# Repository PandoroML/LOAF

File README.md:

# LOAF (Local Observations and Atmospheric Forecasting)

Open source hyperlocal weather forecasting combining machine learning forecast models with local station observations.

- Do you want to improve the weather forecasts at a specific place? 
- Do you have access to local sensors or are intersted in building them? 
- Are you interested in understanding the full process and not relying on big tech companies hiding proprietary algorithms to do so? 

If you answered yes to all of the above, then LOAF is for you.

Part of [Pandoro](https://pandoro.today) — Bread Board Foundry's open science ML tools for climate and environmental research.

This is definitely a work in progress, so stay tuned!

## Planned Architecture

```
┌─────────────────┐      ┌─────────────────────────────────────┐      ┌─────────────────┐
│  DIY Sensors    │ ──── │          Raspberry Pi               │ ──── │ Home Assistant  │
│  (Anemometer,   │      │  • Data storage                     │      │                 │
│   Temperature,  │      │  • ML forecast processing           │      │  Weather entity │
│   etc.)         │      │  • Local prediction generation      │      │  integrations   │
└─────────────────┘      └─────────────────────────────────────┘      └─────────────────┘
```

**Data Flow:**
1. **Sensors → Raspberry Pi**: Local sensors connect to the Pi via a common sensors library, logging observations to local storage
2. **Forecast Processing**: The Pi runs the trained ML model, combining local sensor data with regional forecasts (HRRR/GFS) to generate hyperlocal predictions
3. **Home Assistant Integration**: Predictions are exposed as Home Assistant entities, allowing integration with automations, dashboards, and alerts

## Latest Cool Picture

The first of the ultrasonic transducers have arrived!

## Current priorities:

- Set up HRRR/MADIS data pipeline
- Train regional model and validate against local observations
- Deploy the model to local hardware (raspberry pi)
- Create Home Assistant widget for local wind predictions

---

## Why LOAF?

Standard weather forecasts operate on 3km grids. That resolution can't capture the wind patterns at your specific site—whether it's a backyard wind turbine, a fire-prone hillside, or a remote research station.

Recent ML research shows that fusing gridded forecasts with local sensor data via transformers can reduce prediction error by up to 80%. Commercial services like Tomorrow.io offer this, but they're proprietary and subscription-based. The academic code exists, but there's no easy way to go from "I have a Raspberry Pi" to "I have an improved local forecast."

LOAF bridges that gap: open source hardware, open source models, no vendor lock-in. Build a sensor, train a model for your region, run inference locally.

## About

LOAF generates hyperlocal weather forecasts for locations without nearby weather stations by combining:

- Regional forecast models (NOAA GFS, HRRR, ERA5)
- Sparse local weather station observations
- Multi-modal transformer architecture for spatial-temporal fusion

**Built on research from MIT Earth Intelligence Lab:**
- GitHub: [Earth-Intelligence-Lab/LocalizedWeather](https://github.com/Earth-Intelligence-Lab/LocalizedWeather)
- Paper: Yang, Q., et al. (2024). *Local Off-Grid Weather Forecasting with Multi-Modal Earth Observation Data.* [arXiv:2410.12938](https://arxiv.org/abs/2410.12938)

## Hardware

LOAF uses open source hardware with no vendor lock-in:

- **Sensor**: DIY ultrasonic anemometer
- **Logger**: Raspberry Pi with RS-485/SDI-12 interface and 3D printed enclosure for predictions
- **Power**: Solar panel + battery for remote deployment

## Use Cases

- Off-grid environmental monitoring sites
- Research locations without dedicated weather infrastructure
- Applications requiring forecast transparency and hardware specifications for reproducibility

## Features

- Corrects systematic biases in large-scale forecast models for local conditions
- Hardware-transparent infrastructure for reproducible research
- Clear documentation for researchers without ML engineering backgrounds
- Combines numerical weather predictions with station measurements

## Related Projects

- [offgrid-weather-station](https://github.com/vinthewrench/offgrid-weather-station) - Off-grid weather station project
- [QingStation](https://github.com/majianjia/QingStation) - Open source ultrasonic anemometer
- [DL1GLH Ultrasonic Anemometer](https://www.dl1glh.de/ultrasonic-anemometer.html) - DIY ultrasonic wind sensor design

## Documentation

See the full documentation here: https://pandoroml.github.io/LOAF/

### Development Plans

- [ML Pipeline Development Plan](plan/dev-plan-ml-pipeline.md) - Detailed plan for reproducing LocalizedWeather for Seattle/PNW

### How to Run

The pipeline is: **download data → train a model → serve forecasts over REST**. Commands
below assume you're in the repo root and have installed the package (`pip install -e ".[dev]"`).
They use `config/arlington.yaml` (DCA, IAD, BWI, HEF, MRB stations); swap in
`config/seattle.yaml` for the PNW region instead.

#### Quickest path: one command

`loaf-pipeline` chains download → train → serve for you:

```bash
loaf-pipeline --config software/config/arlington.yaml \
    --start-date 2024-10-01 --end-date 2024-12-31 --year 2024 --port 5000
```

It blocks on the running server at the end, so leave it running and query it from another
terminal (see step 4 below). Useful flags for resuming a partial run:

- `--skip-download` — reuse whatever's already in `data/`
- `--skip-train --checkpoint <path>` — skip straight to serving an existing checkpoint
- `--no-serve` — stop after training, print the checkpoint path, and exit
- `--use-hrrr` / `--use-era5` — also download and fuse gridded forecasts (see step 1)

Run `loaf-pipeline --help` for the full flag list (it's the union of the three commands below).

Run loaf-report-summary --runs-dir runs after any batch of training runs to summarize results all modeling attempts in /runs.

#### Or, step by step

Useful if you want to inspect data between steps, retrain from already-downloaded data, or
swap in a different checkpoint without retraining.

**1. Download station observations** (IEM/ASOS — no registration required):

```bash
loaf-download-iem --config software/config/arlington.yaml \
    --start-date 2024-10-01 --end-date 2024-12-31
```

This is the minimum needed to train. Optionally fuse gridded forecasts too — HRRR needs no
auth (AWS S3), ERA5 needs a free [CDS API key](https://cds.climate.copernicus.eu/) in
`~/.cdsapirc`:

```bash
loaf-download-hrrr --config software/config/arlington.yaml \
    --start-date 2024-10-01 --end-date 2024-12-31
loaf-download-era5 --config software/config/arlington.yaml \
    --start-year 2024 --end-year 2024
```

All three write into `data/` in the current directory by default.

**2. Train a model** (MPNN or ViT backbone):

```bash
loaf-train --config software/config/arlington.yaml --year 2024
# add --model-type vit, --epochs N, --use-hrrr, or --use-era5 as needed
```

Writes `best.pt` / `last.pt` checkpoints and a `train_log.csv` to `runs/arlington_<timestamp>/`.

**3. Serve forecasts over REST:**

```bash
loaf-serve --checkpoint runs/arlington_<timestamp>/best.pt --port 5000
```

**4. Query it** (e.g. Reagan National Airport, Arlington VA):

```bash
curl "http://localhost:5000/api/forecast?lat=38.8512&lon=-77.0402"
curl http://localhost:5000/api/forecast/all   # every station in the graph
curl http://localhost:5000/health
```

Each response includes multi-horizon `u`/`v` wind predictions plus derived `wind_speed` and
`wind_direction`, ready to wire into a Home Assistant REST sensor.

## License

MIT

## Citation

If you find this project useful for your research or applications, please kindly cite using this BibTeX::
```bibtex
@software{Johnson_LOAF_Local_Observations_2026,
author = {Johnson, Keenan and Kim, Susie},
month = jan,
title = {{LOAF (Local Observations and Atmospheric Forecasting)}},
url = {https://github.com/PandoroML/LOAF},
year = {2026}
}
```

## Contact

- Website: https://pandoro.today
- Email: pandoro@breadboardfoundry.com

---

Built by [Bread Board Foundry](https://breadboardfoundry.com)

## Cool Picture Archive

The first pcb went to fab for our ultrasonic anemometer build inspired by QingStation. The first version is very similiar to the Ultrasonic Anemometer in QingStation, but it simplified by removing parts we don't need for now and updated to included parts that are easily purchaseable, as some parts in Qing have gone end of life.

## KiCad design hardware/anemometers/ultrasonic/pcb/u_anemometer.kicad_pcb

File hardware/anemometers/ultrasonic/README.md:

This is heavily inspired by the https://github.com/majianjia/QingStation/tree/main project

It has the following big changes:

- Removed the Rain sensor
- Removed the microphone 
- Removed the lighting sensor
- Removed the RGB sensor

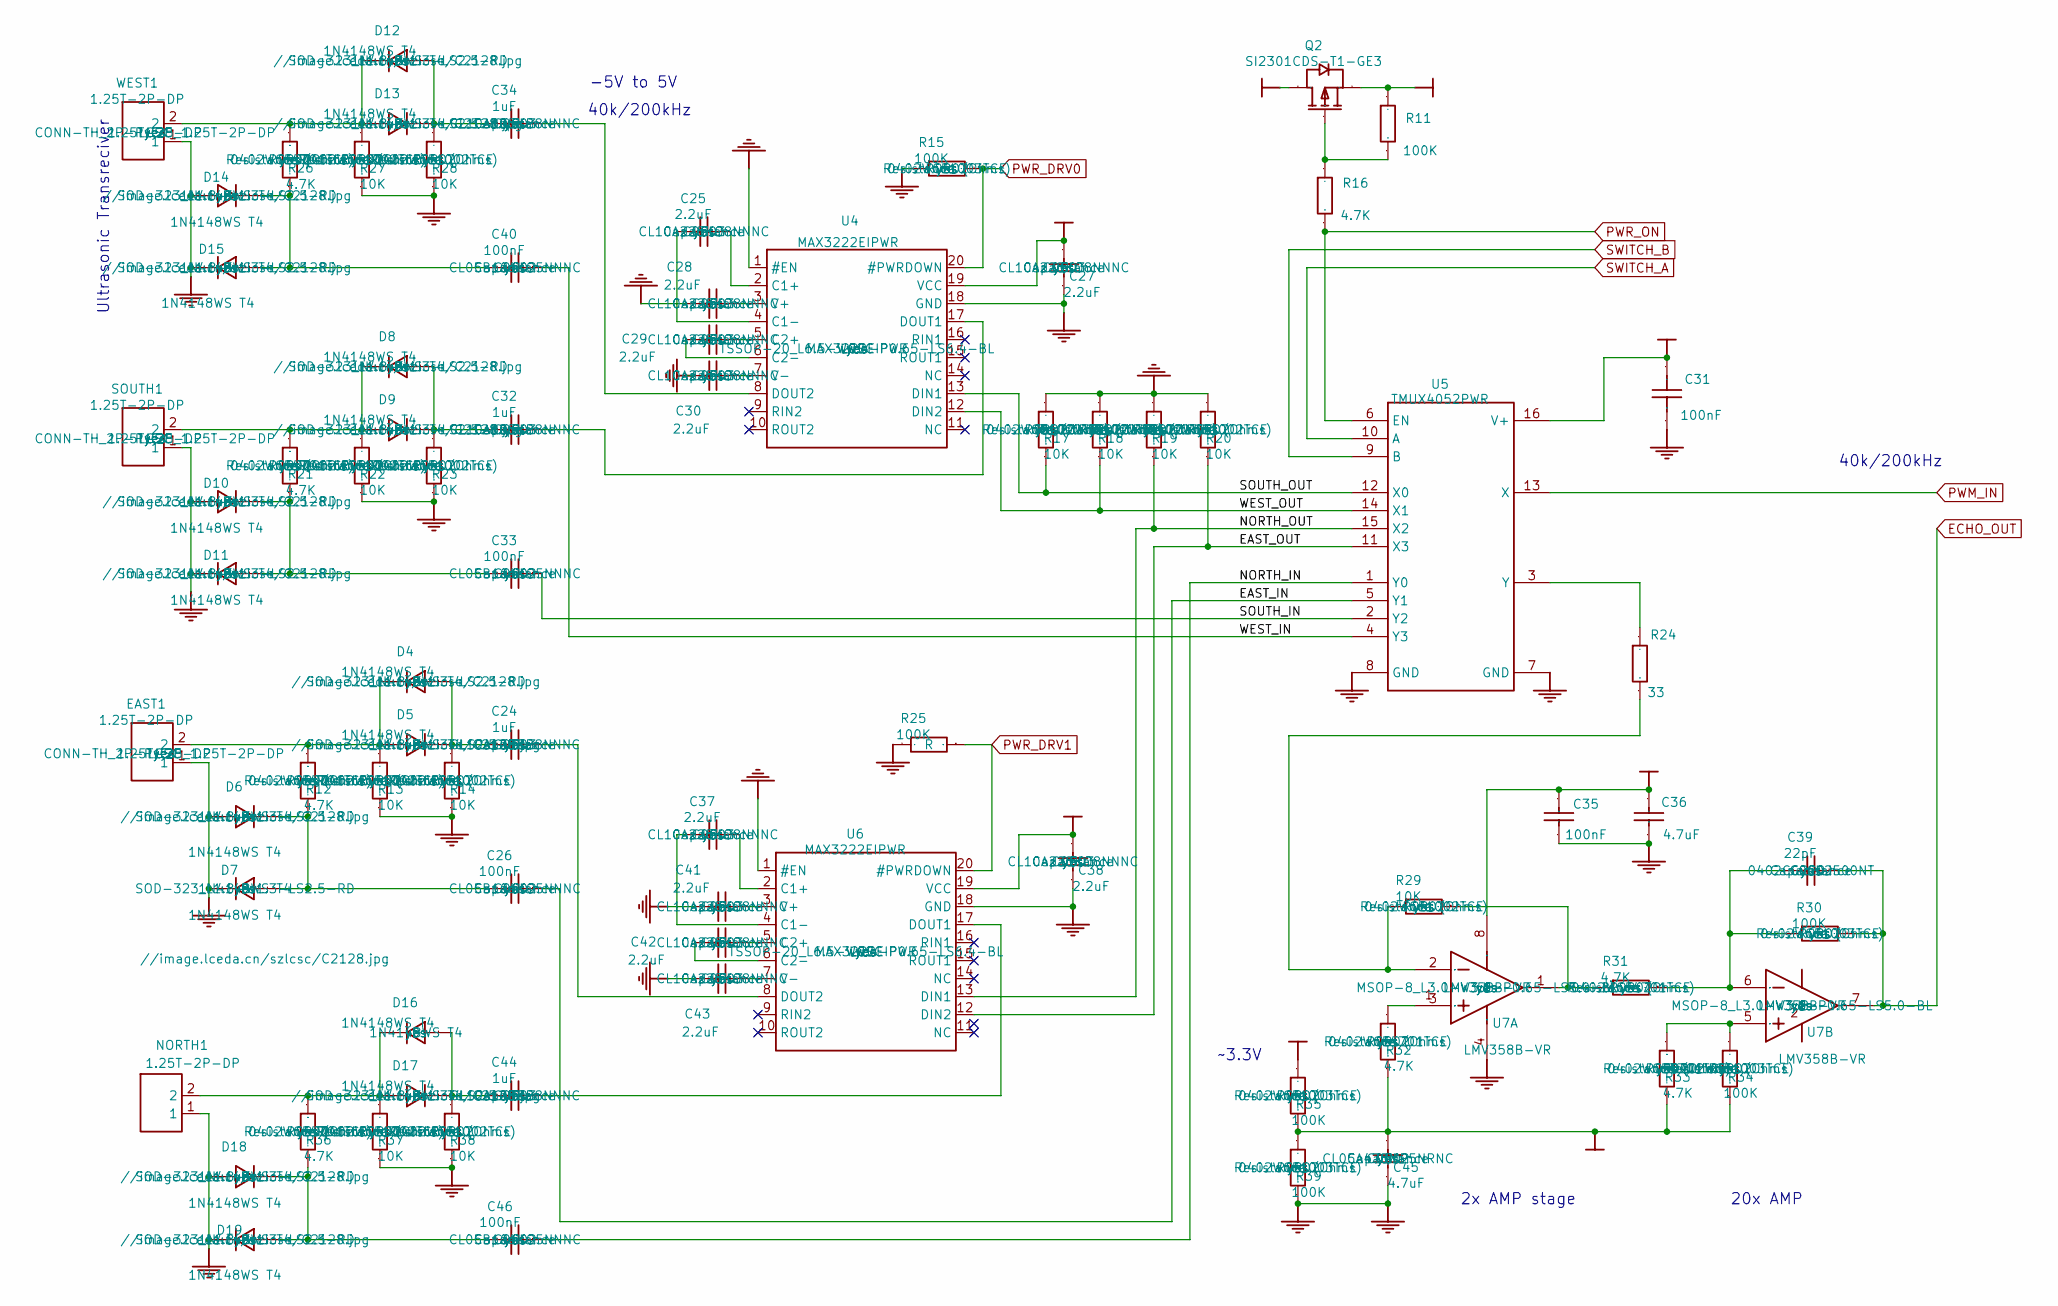
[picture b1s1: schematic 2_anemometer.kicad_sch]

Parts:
C24, C32, C34, C44: 1uF; C0603; Manufacturer Part CL10A105KB8NNNC
C25, C27, C28, C29, C30, C37, C38, C41, C42, C43: 2.2uF; C0603; Manufacturer Part CL10A225KO8NNNC
C26, C33, C35, C40, C46: 100nF; C0402; Manufacturer Part CL05B104KO5NNNC
C31: 100nF; C0603; Manufacturer Part CC0603KRX7R9BB104
C36: 4.7uF; C0603; Manufacturer Part CL10A475KO8NNNC
C39: 22pF; C0402; Manufacturer Part 0402CG220J500NT
C45: 4.7uF; C0402; Manufacturer Part CL05A475MP5NRNC
D4, D5, D6, D7, D8, D9, D10, D11, D12, D13, D14, D15, D16, D17, D18, D19: 1N4148WS T4; SOD-323_L1.8-W1.3-LS2.5-RD; Manufacturer Part 1N4148WS T4
EAST1: 1.25T-2P-DP; CONN-TH_2P-P1.25_1.25T-2P-DP; Manufacturer Part 1.25T-2P-DP
NORTH1: 1.25T-2P-DP; CONN-TH_2P-P1.25_1.25T-2P-DP; Manufacturer Part 1.25T-2P-DP
Q2: SI2301CDS-T1-GE3; SOT-23-3_L3.0-W1.7-P0.95-LS2.9-BR; Manufacturer Part SI2301CDS-T1-GE3
R11, R15, R25, R30, R34, R35, R39: 100K; R0402; Manufacturer Part 0402WGF1003TCE
R12, R16, R21, R26, R31, R32, R33, R36: 4.7K; R0402; Manufacturer Part 0402WGF4701TCE
R13, R14, R17, R18, R19, R20, R22, R23, R27, R28, R29, R37, R38: 10K; R0402; Manufacturer Part 0402WGF1002TCE
R24: 33; R0402; Manufacturer Part 0402WGF330JTCE
SOUTH1: 1.25T-2P-DP; CONN-TH_2P-P1.25_1.25T-2P-DP; Manufacturer Part 1.25T-2P-DP
U4, U6: MAX3222EIPWR; TSSOP-20_L6.5-W4.4-P0.65-LS6.4-BL; Manufacturer Part MAX3222EIPWR
U5: TMUX4052PWR; TSSOP-16_L5.0-W4.4-P0.65-LS6.4-BL; Manufacturer Part TMUX4052PWR
U7: LMV358B-VR; MSOP-8_L3.0-W3.0-P0.65-LS5.0-BL; Manufacturer Part LMV358B-VR
WEST1: 1.25T-2P-DP; CONN-TH_2P-P1.25_1.25T-2P-DP; Manufacturer Part 1.25T-2P-DP

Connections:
3.3V: C27.2, C31.2, C38.2, Q2.2 (S), R11.2, U4.19 (VCC), U5.16 (V+), U6.19 (VCC); also elsewhere on the board
/2_anemometer/EAST_IN: C26.1, U5.5 (Y1)
/2_anemometer/EAST_OUT: R20.1, U5.11 (X3), U6.12 (DIN2)
/2_anemometer/NORTH_IN: C46.1, U5.1 (Y0)
/2_anemometer/NORTH_OUT: R19.1, U5.15 (X2), U6.13 (DIN1)
/2_anemometer/SOUTH_IN: C33.1, U5.2 (Y2)
/2_anemometer/SOUTH_OUT: R17.1, U4.13 (DIN1), U5.12 (X0)
/2_anemometer/WEST_IN: C40.1, U5.4 (Y3)
/2_anemometer/WEST_OUT: R18.1, U4.12 (DIN2), U5.14 (X1)
ECHO_OUT: C39.2, R30.2, U7.7 (OUTB); also elsewhere on the board
GND: C27.1, C28.2, C30.1, C31.1, C35.2, C36.1, C38.1, C41.2, C43.1, C45.1, D6.2 (A), D7.1 (K), D10.2 (A), D11.1 (K), D14.2 (A), D15.1 (K), D18.2 (A), D19.1 (K), EAST1.1, NORTH1.1, R13.1, R14.1, R15.1, R17.2, R18.2, R19.2, R20.2, R22.1, R23.1, R25.2, R27.1, R28.1, R37.1, R38.1, R39.1, SOUTH1.1, U4.1 (#EN), U4.18 (GND), U5.7 (GND), U5.8 (GND), U6.1 (#EN), U6.18 (GND), U7.4 (-VS), WEST1.1; also elsewhere on the board
unnamed: C24.1, D4.2 (A), D5.1 (K), R14.2
unnamed: D4.1 (K), D5.2 (A), EAST1.2, R12.1, R13.2
unnamed: C26.2, D6.1 (K), D7.2 (A), R12.2
unnamed: C32.1, D8.2 (A), D9.1 (K), R23.2
unnamed: D8.1 (K), D9.2 (A), R21.1, R22.2, SOUTH1.2
unnamed: C33.2, D10.1 (K), D11.2 (A), R21.2
unnamed: C34.1, D12.2 (A), D13.1 (K), R28.2
unnamed: D12.1 (K), D13.2 (A), R26.1, R27.2, WEST1.2
unnamed: C40.2, D14.1 (K), D15.2 (A), R26.2
unnamed: C44.1, D16.2 (A), D17.1 (K), R38.2
unnamed: D16.1 (K), D17.2 (A), NORTH1.2, R36.1, R37.2
unnamed: C46.2, D18.1 (K), D19.2 (A), R36.2
unnamed: Q2.1 (G), R11.1, R16.2
unnamed: C25.1, U4.2 (C1+)
unnamed: C25.2, U4.4 (C1−)
unnamed: C29.1, U4.5 (C2+)
unnamed: C29.2, U4.6 (C2−)
unnamed: C32.2, U4.17 (DOUT1)
unnamed: C34.2, U4.8 (DOUT2)
unnamed: C28.1, U4.3 (V+)
unnamed: C30.2, U4.7 (V−)
unnamed: R24.2, U5.3 (Y)
unnamed: C37.1, U6.2 (C1+)
unnamed: C37.2, U6.4 (C1−)
unnamed: C42.1, U6.5 (C2+)
unnamed: C42.2, U6.6 (C2−)
unnamed: C44.2, U6.17 (DOUT1)
unnamed: C24.2, U6.8 (DOUT2)
unnamed: C41.1, U6.3 (V+)
unnamed: C43.2, U6.7 (V−)
unnamed: R32.2, U7.3 (INA+)
unnamed: R24.1, R29.2, U7.2 (INA-)
unnamed: R29.1, R31.2, U7.1 (OUTA)
unnamed: R33.1, R34.2, U7.5 (INB+)
unnamed: C39.1, R30.1, R31.1, U7.6 (INB-)
PWM_IN: U5.13 (X); also elsewhere on the board
PWR_DRV0: R15.2, U4.20 (#PWRDOWN); also elsewhere on the board
PWR_DRV1: R25.1, U6.20 (#PWRDOWN); also elsewhere on the board
PWR_ON: R16.1, U5.6 (EN); also elsewhere on the board
SWITCH_A: U5.10 (A); also elsewhere on the board
SWITCH_B: U5.9 (B); also elsewhere on the board
VGND: C45.2, R32.1, R33.2, R34.1, R35.1, R39.2
VREF+: R35.2; also elsewhere on the board
V_OPA: C35.1, C36.2, Q2.3 (D), U7.8 (+VS)

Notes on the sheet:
Ultrasonic Transreciver
-5V to 5V
20x AMP
~3.3V
40k/200kHz
2x AMP stage

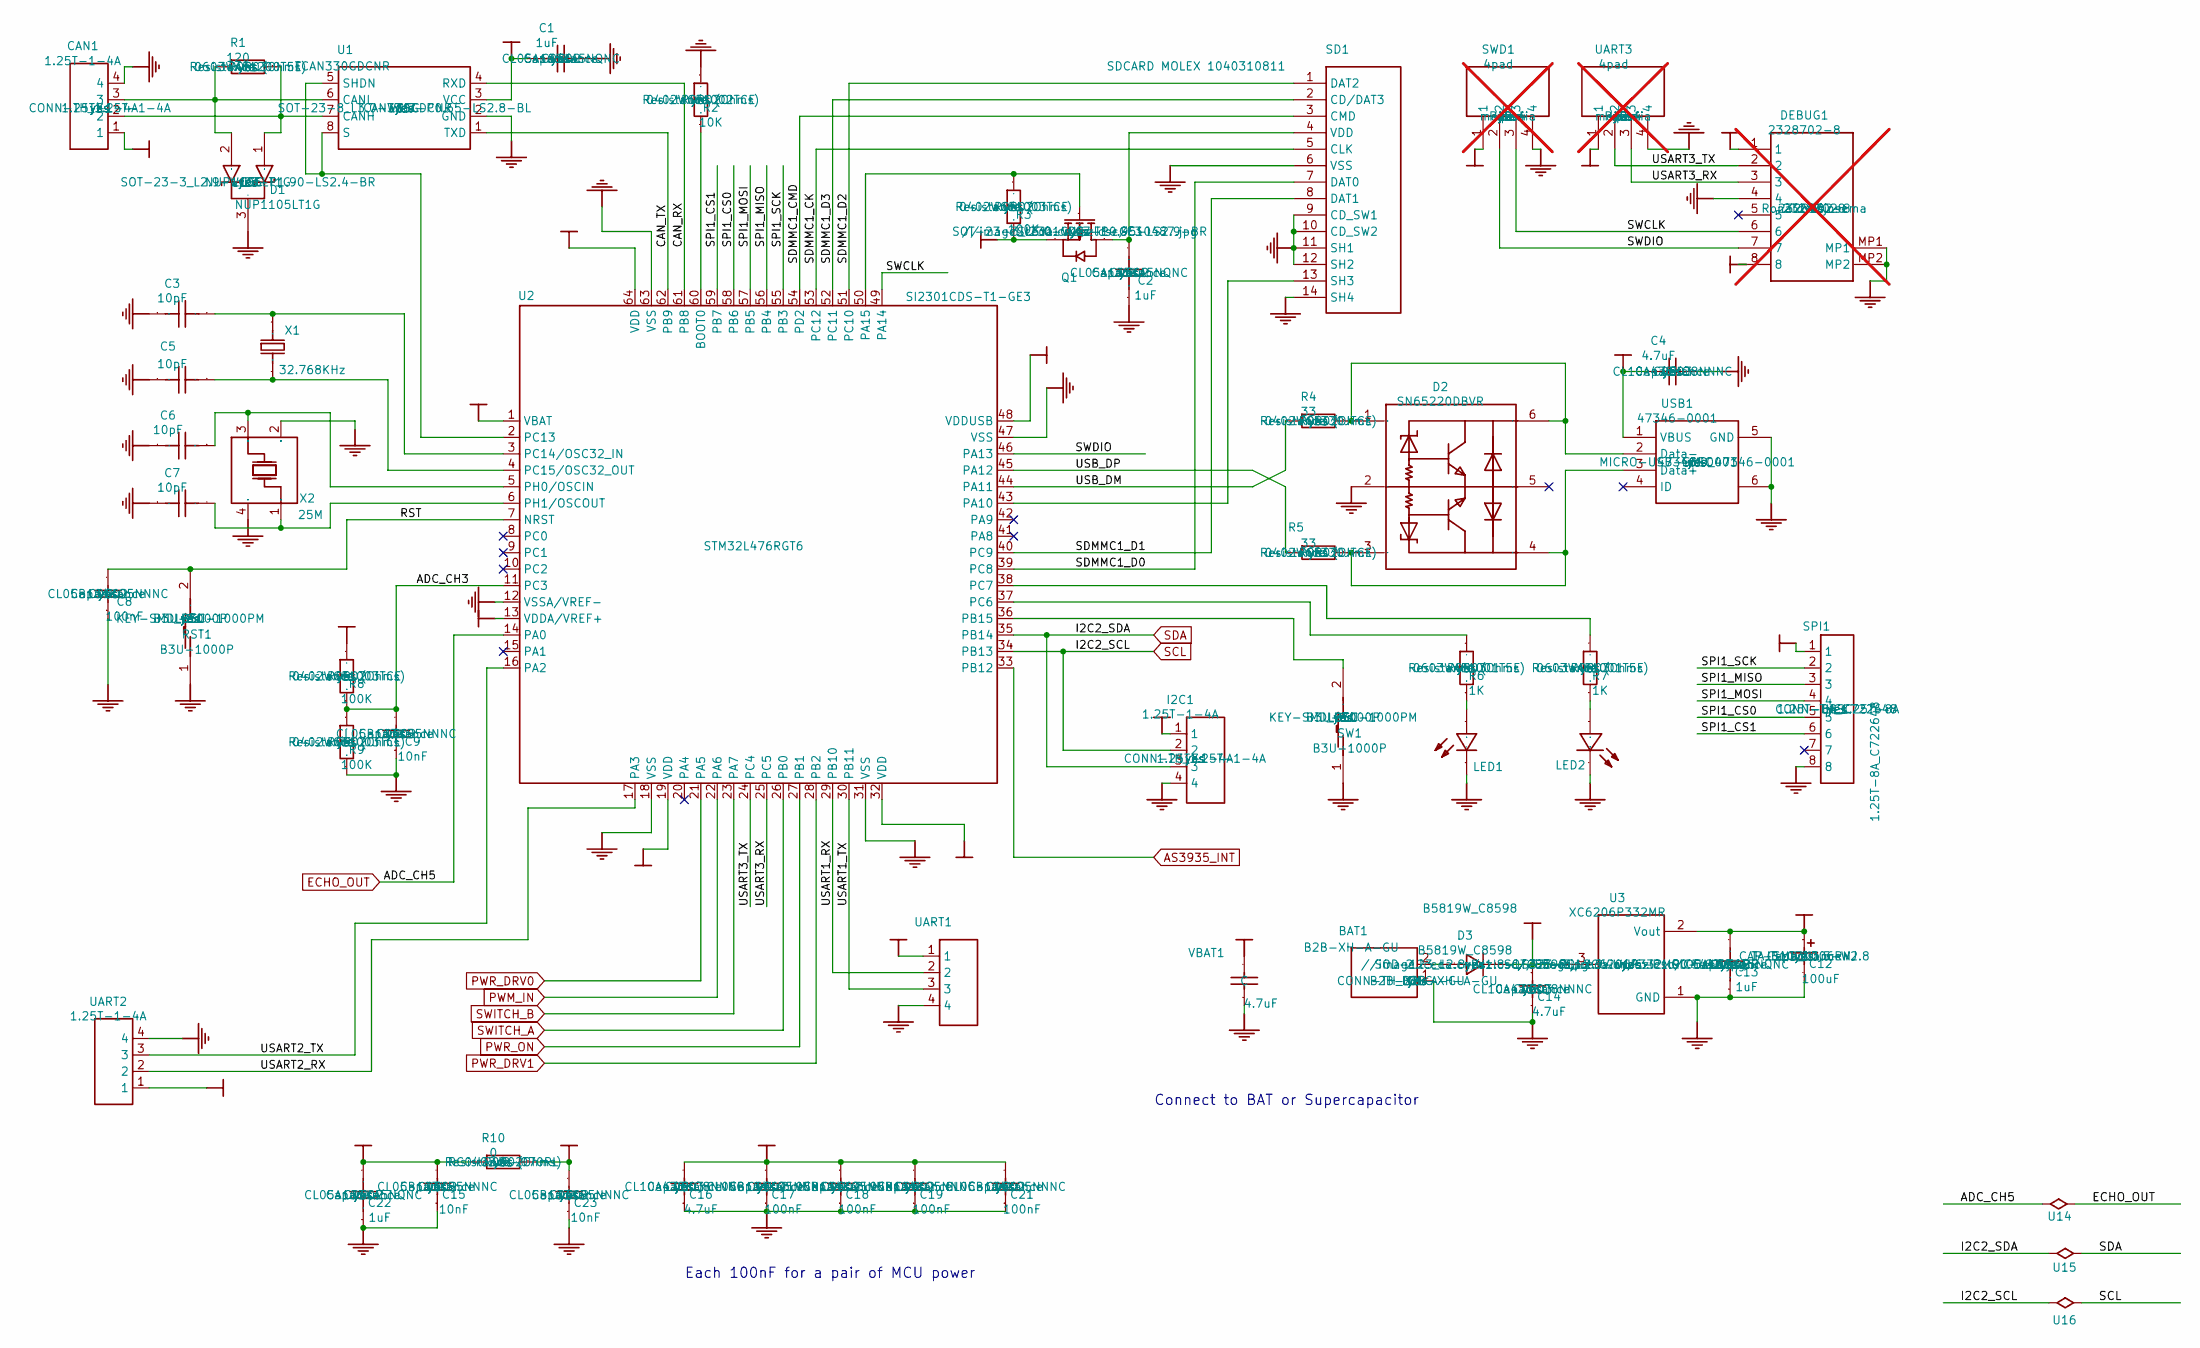
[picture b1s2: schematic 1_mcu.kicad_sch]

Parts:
BAT1: B2B-XH-A-GU; CONN-TH_B2B-XH-A-GU; Manufacturer Part B2B-XH-A-GU
C1, C2, C13, C22: 1uF; C0402; Manufacturer Part CL05A105KA5NQNC
C3, C5, C6, C7: 10pF; C0402; Manufacturer Part CL05C100JB5NNNC
C4, C14, C16: 4.7uF; C0603; Manufacturer Part CL10A475KO8NNNC
C8, C17, C18, C19, C21: 100nF; C0402; Manufacturer Part CL05B104KO5NNNC
C9, C15, C23: 10nF; C0402; Manufacturer Part CL05B103KB5NNNC
C12: 100uF; CAP-SMD_L3.5-W2.8; Manufacturer Part TAJB107K006RNJ
CAN1: 1.25T-1-4A; CONN-TH_1.25T-1-4A; Manufacturer Part 1.25T-1-4A
D1: NUP1105LT1G; SOT-23-3_L2.9-W1.3-P1.90-LS2.4-BR; Manufacturer Part NUP1105LT1G
D2: SN65220DBVR; SOT-23-6_L2.9-W1.6-P0.95-LS2.8-BR; Manufacturer Part SN65220DBVR
D3: B5819W_C8598; SOD-123_L2.8-W1.8-LS3.7-RD; Manufacturer Part B5819W
DEBUG1: 2328702-8; 23287028; not fitted
I2C1: 1.25T-1-4A; CONN-TH_1.25T-1-4A; Manufacturer Part 1.25T-1-4A
LED1: XL-1608UBC-06A; LED0603-R-RD; Manufacturer Part XL-1608UBC-06A
LED2: KT-0603R; LED0603-R-RD; Manufacturer Part KT-0603R
Q1: SI2301CDS-T1-GE3; SOT-23-3_L3.0-W1.7-P0.95-LS2.9-BR; Manufacturer Part SI2301CDS-T1-GE3
R1: 120; R0603; Manufacturer Part 0603WAF1200T5E
R2: 10K; R0402; Manufacturer Part 0402WGF1002TCE
R3, R8, R9: 100K; R0402; Manufacturer Part 0402WGF1003TCE
R4, R5: 33; R0402; Manufacturer Part 0402WGF330JTCE
R6, R7: 1K; R0603; Manufacturer Part 0603WAF1001T5E
R10: 0; R0402; Manufacturer Part RC0402JR-070RL
RST1: B3U-1000P; KEY-SMD_B3U-1000PM; Manufacturer Part B3U-1000P
SD1: SDCARD MOLEX 1040310811; 1040310811; Manufacturer Part 1040310811
SPI1: 1.25T-8A_C722648; CONN-TH_1.25T-8A; Manufacturer Part 1.25T-8A
SW1: B3U-1000P; KEY-SMD_B3U-1000PM; Manufacturer Part B3U-1000P
SWD1: 4pad; PAD 4; not fitted
U1: TCAN330GDCNR; SOT-23-8_L3.0-W1.7-P0.65-LS2.8-BL; Manufacturer Part TCAN330GDCNR
U2: STM32L476RGT6; LQFP-64_L10.0-W10.0-P0.50-LS12.0-BL; Manufacturer Part STM32L476RGT6
U3: XC6206P332MR; SOT-23-3_L2.9-W1.6-P1.90-LS2.8-BR; Manufacturer Part XC6206P332MR
U14, U15, U16: Sort_Symbol
UART1, UART2: 1.25T-1-4A; CONN-TH_1.25T-1-4A; Manufacturer Part 1.25T-1-4A
UART3: 4pad; PAD 4; not fitted
USB1: 47346-0001; MICRO-USB-SMD_47346-0001; Manufacturer Part 47346-0001
VBAT1: 4.7uF; C0603; Manufacturer Part CL10A475KO8NNNC
X1: 32.768KHz; OSC-SMD_L2.0-W1.2; Manufacturer Part SC-20S32.768kHz20PPM12.5pF
X2: 25M; OSC-SMD_4P-L3.2-W2.5-BL; Manufacturer Part NX3225GA-24MHZ-STD-CRG-2

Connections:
3.3V: C1.2, C12.1, C13.2, C16.2, C17.2, C18.2, C19.2, C21.2, C23.2, DEBUG1.8, I2C1.1, Q1.2 (S), R3.1, R10.2, SPI1.1, SWD1.1, U1.3 (VCC), U2.19 (VDD), U2.32 (VDD), U2.48 (VDDUSB), U2.64 (VDD), U3.2 (Vout), UART1.1, UART2.1; also elsewhere on the board
+5V: C4.2, C14.1, CAN1.1, D3.1 (-), DEBUG1.1, R8.2, U3.3 (Vin), UART3.1, USB1.1 (VBUS)
/1_mcu/ADC_CH3: C9.2, R8.1, R9.2, U2.11 (PC3)
/1_mcu/CAN_RX: U1.4 (RXD), U2.61 (PB8)
/1_mcu/CAN_TX: U1.1 (TXD), U2.62 (PB9)
/1_mcu/RST: C8.2, RST1.2, U2.7 (NRST)
/1_mcu/SDMMC1_CK: SD1.5 (CLK), U2.53 (PC12)
/1_mcu/SDMMC1_CMD: SD1.3 (CMD), U2.54 (PD2)
/1_mcu/SDMMC1_D0: SD1.7 (DAT0), U2.39 (PC8)
/1_mcu/SDMMC1_D1: SD1.8 (DAT1), U2.40 (PC9)
/1_mcu/SDMMC1_D2: SD1.1 (DAT2), U2.51 (PC10)
/1_mcu/SDMMC1_D3: SD1.2 (CD/DAT3), U2.52 (PC11)
/1_mcu/SPI1_CS0: SPI1.5, U2.58 (PB6)
/1_mcu/SPI1_CS1: SPI1.6, U2.59 (PB7)
/1_mcu/SPI1_MISO: SPI1.3, U2.56 (PB4)
/1_mcu/SPI1_MOSI: SPI1.4, U2.57 (PB5)
/1_mcu/SPI1_SCK: SPI1.2, U2.55 (PB3)
/1_mcu/SWCLK: DEBUG1.6, SWD1.3, U2.49 (PA14)
/1_mcu/SWDIO: DEBUG1.7, SWD1.2, U2.46 (PA13)
/1_mcu/USART1_RX: U2.29 (PB10), UART1.2
/1_mcu/USART1_TX: U2.30 (PB11), UART1.3
/1_mcu/USART2_RX: U2.17 (PA3), UART2.2
/1_mcu/USART2_TX: U2.16 (PA2), UART2.3
/1_mcu/USART3_RX: DEBUG1.3, U2.25 (PC5), UART3.3
/1_mcu/USART3_TX: DEBUG1.2, U2.24 (PC4), UART3.2
/1_mcu/USB_DM: R4.1, U2.44 (PA11)
/1_mcu/USB_DP: R5.1, U2.45 (PA12)
AS3935_INT: U2.33 (PB12)
ECHO_OUT: U2.14 (PA0), U14.; also elsewhere on the board
GND: BAT1.1, C1.1, C2.1, C3.1, C4.1, C5.1, C6.2, C7.1, C8.1, C9.1, C12.2, C13.1, C14.2, C15.1, C16.1, C17.1, C18.1, C19.1, C21.1, C22.1, C23.1, CAN1.4, D1.3 (C), D2.2, DEBUG1.4, DEBUG1.MP1, DEBUG1.MP2, I2C1.4, LED1.2 (C), LED2.2 (K), R2.2, R9.1, RST1.1, SD1.6 (VSS), SD1.9 (CD_SW1), SD1.10 (CD_SW2), SD1.11 (SH1), SD1.12 (SH2), SD1.14 (SH4), SPI1.8, SW1.1, SWD1.4, U1.2 (GND), U2.12 (VSSA/VREF-), U2.18 (VSS), U2.31 (VSS), U2.47 (VSS), U2.63 (VSS), U3.1 (GND), UART1.4, UART2.4, UART3.4, USB1.5 (GND), USB1.6, VBAT1.1, X2.2 (GND), X2.4 (GND); also elsewhere on the board
unnamed: BAT1.2, D3.2 (+)
unnamed: LED1.1 (A), R6.1
unnamed: LED2.1 (A), R7.1
unnamed: C2.2, Q1.3 (D), SD1.4 (VDD)
unnamed: Q1.1 (G), R3.2, U2.50 (PA15)
unnamed: SD1.13 (SH3), U2.43 (PA10)
unnamed: CAN1.2, D1.1 (A), R1.2, U1.7 (CANH)
unnamed: CAN1.3, D1.2 (A), R1.1, U1.6 (CANL)
unnamed: U1.5 (SHDN), U1.8 (S), U2.2 (PC13)
unnamed: R2.1, U2.60 (BOOT0)
unnamed: SW1.2, U2.36 (PB15)
unnamed: R6.2, U2.37 (PC6)
unnamed: R7.2, U2.38 (PC7)
unnamed: C3.2, U2.3 (PC14/OSC32_IN), X1.2
unnamed: C5.2, U2.4 (PC15/OSC32_OUT), X1.1
unnamed: C6.1, U2.5 (PH0/OSCIN), X2.3 (OSC2)
unnamed: C7.2, U2.6 (PH1/OSCOUT), X2.1 (OSC1)
unnamed: D2.3, D2.4, R5.2, USB1.3 (Data+)
unnamed: D2.1, D2.6, R4.2, USB1.2 (Data-)
PWM_IN: U2.22 (PA6); also elsewhere on the board
PWR_DRV0: U2.21 (PA5); also elsewhere on the board
PWR_DRV1: U2.28 (PB2); also elsewhere on the board
PWR_ON: U2.27 (PB1); also elsewhere on the board
SCL: I2C1.2, U2.34 (PB13), U16.; also elsewhere on the board
SDA: I2C1.3, U2.35 (PB14), U15.; also elsewhere on the board
SWITCH_A: U2.26 (PB0); also elsewhere on the board
SWITCH_B: U2.23 (PA7); also elsewhere on the board
VBAT: U2.1 (VBAT), VBAT1.2
VREF+: C15.2, C22.2, R10.1, U2.13 (VDDA/VREF+); also elsewhere on the board

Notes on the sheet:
Each 100nF for a pair of MCU power
Connect to BAT or Supercapacitor

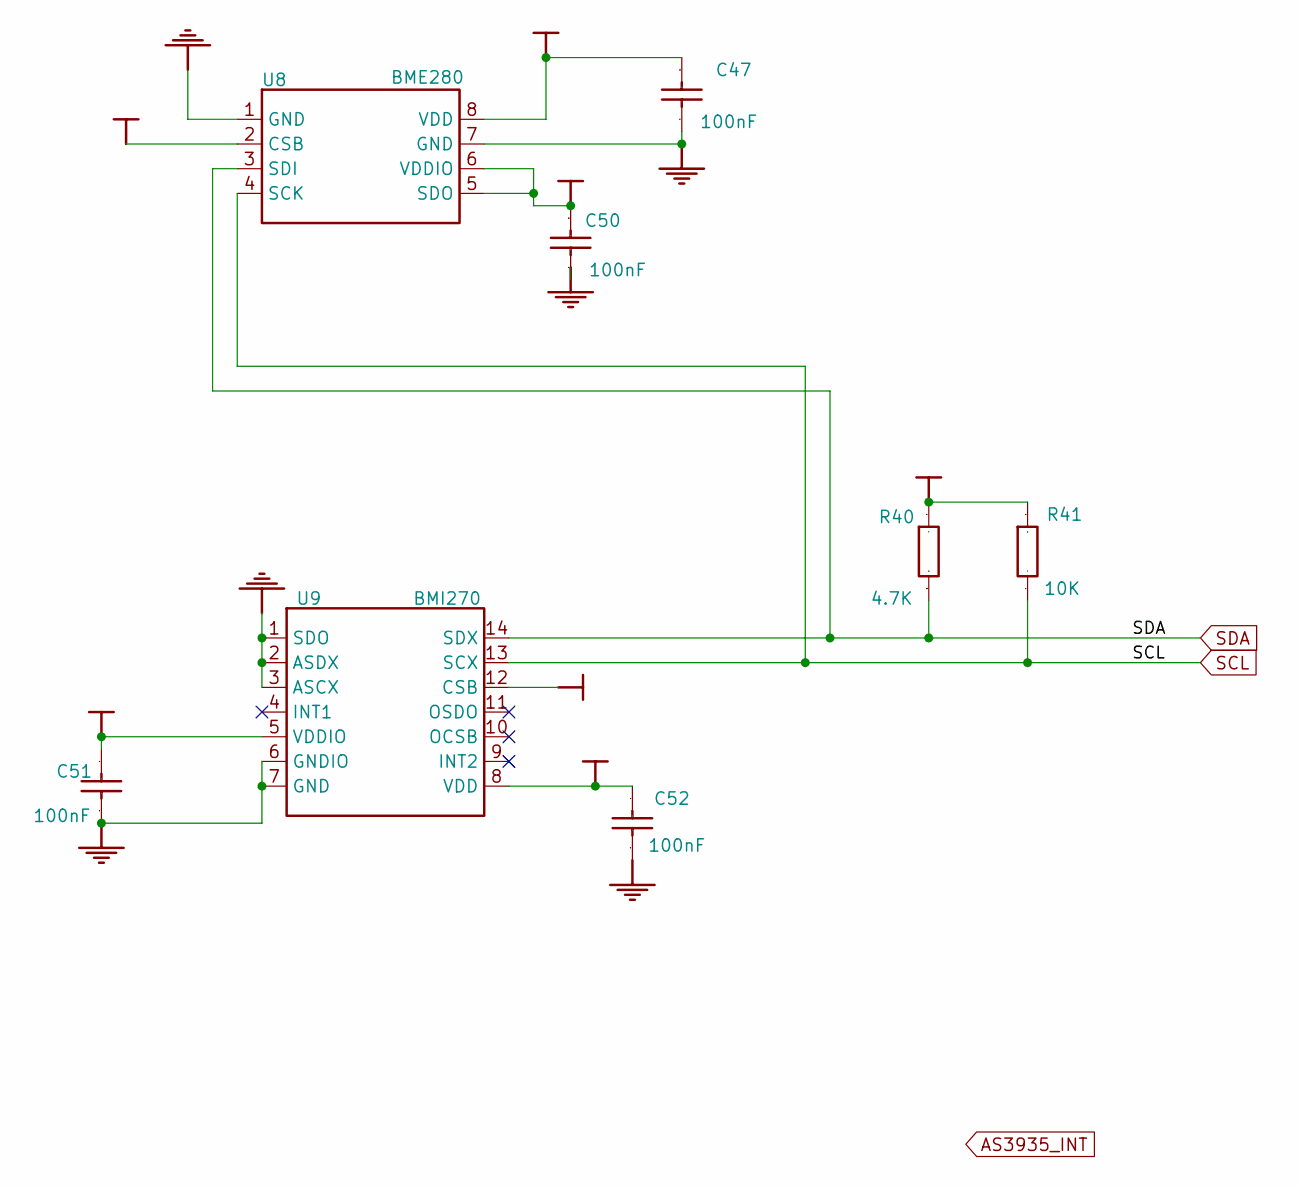
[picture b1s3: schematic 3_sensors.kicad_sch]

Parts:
C47, C50, C51, C52: 100nF; C0402; Manufacturer Part CL05B104KO5NNNC
R40: 4.7K; R0402; Manufacturer Part 0402WGF4701TCE
R41: 10K; R0402; Manufacturer Part 0402WGF1002TCE
U8: BME280; LGA-8_BME280_BR; Manufacturer Part BME280
U9: BMI270; LGA-14_L3.0-W2.5-P0.50-BL; Manufacturer Part BMI270

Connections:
3.3V: C47.1, C50.1, C51.1, C52.1, R40.2, R41.1, U8.2 (CSB), U8.5 (SDO), U8.6 (VDDIO), U8.8 (VDD), U9.5 (VDDIO), U9.8 (VDD), U9.12 (CSB); also elsewhere on the board
GND: C47.2, C50.2, C51.2, C52.2, U8.1 (GND), U8.7 (GND), U9.1 (SDO), U9.2 (ASDX), U9.3 (ASCX), U9.6 (GNDIO), U9.7 (GND); also elsewhere on the board
SCL: R41.2, U8.4 (SCK), U9.13 (SCX); also elsewhere on the board
SDA: R40.1, U8.3 (SDI), U9.14 (SDX); also elsewhere on the board

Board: 4 copper layers, 137 parts (34 on the bottom side), 103 nets, no tracks yet.

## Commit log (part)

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2025-12-19 README.md
2025-12-19 Readme
2026-01-09 Add WIP note
2026-01-12 Update README with current priorities and hardware info
    Added current priorities and hardware section to README.
2026-01-13 Add UV and Mat. 4 MKDocs
2026-01-13 Add basic site
2026-01-13 Add Initial Dev Log Setup (#3)
    * Add UV and Mat. 4 MKDocs
    * Add basic site
2026-01-13 Add citation file
2026-01-13 Add citation bibtex
2026-01-13 Add license (MIT)
2026-01-13 Remove contributing for now
2026-01-13 remove coming soon links
2026-01-13 Add ghpages CI
2026-01-13 move mkdocs file
2026-01-13 Move docs
2026-01-13 Add docs deploy preview
2026-01-13 Improve docs main page content
2026-01-13 Add link to docs
2026-01-13 Update to ubuntu 24
2026-01-13 Improve docs main page content (#8)
    * Improve docs main page content
    * Update index.md
    * Add link to docs
    * Update to ubuntu 24
2026-01-13 .gitignore: Add DS Store
2026-01-13 Add initial dev log structure!
2026-01-13 Dev log setup (#9)
    * .gitignore: Add DS Store
    * Add initial dev log structure!
2026-01-13 Update todos a bit further
2026-01-13 Add initial post
2026-01-13 Add 1-12 dev log
2026-01-13 Add basic context to the readme
2026-01-13 Add start of project post: Jan. 12 (#10)
2026-01-15 Update colors
2026-01-15 Update colors (#13)
2026-01-15 Improve the why section
2026-01-15 Fix warning
2026-01-15 Add why to main readme
2026-01-15 Add some basic hardware folders
2026-01-15 Add wind blog!
2026-01-15 Add teardown images
2026-01-15 Updates to blog
2026-01-15 Dev Log: 1-14 Teardown of a Wind Sensor (#17)
2026-01-15 Add RSS Plugin
2026-01-15 Fix build
2026-01-15 Add RSS Plugin (#19)
    * Add RSS Plugin
    * Update mkdocs.yml
    * Fix build
    * Update docs-preview.yml
    * Update mkdocs.yml
2026-01-15 Add basic kicad start for anemometer
2026-01-15 .gitignore: add kicad stuff
2026-01-15 Add plausible
2026-01-15 Readme: Add related projects section
2026-01-16 Remove old template project
2026-01-16 Add readme
2026-01-16 Initial import of qing pcb
2026-01-16 Better import
2026-01-16 Update names
2026-01-16 DRC clear
2026-01-16 Updaetes
2026-01-16 Latest updates!
2026-01-16 Fix SD Card part number
2026-01-16 Add bom
2026-01-16 Fix mux
2026-01-16 Fix LED
2026-01-16 Update to BMI270
2026-01-16 Fab outputs
2026-01-16 Fixed!
2026-01-16 Fixes!
2026-01-17 Fab updates
2026-01-17 Remove BME280
2026-01-17 blank board
2026-01-17 Readme: improve slightly
    Clarify the transition from Raspberry Pi to improved local forecasts.
2026-01-18 Initial anemometer pcb (#21)
    * Remove old template project
    * Add readme
    * Initial import of qing pcb
    * Better import
    * Update names
    * DRC clear
2026-01-18 Readme: Improved the who is this for section
2026-01-18 hw readme: fix typo
2026-01-18 Add latest picture and project details to README
    Added a section for the latest cool picture and details about the ultrasonic anemometer build.
2026-01-20 Dev log: Jan 17
2026-01-23 Change copyright to 2026 Bread Board Foundry
    Updated copyright year and organization in LICENSE file.
2026-01-25 Add deployment of model to local hardware
2026-01-26 Add arch diagram
2026-01-26 Add diagram to docs
2026-01-26 Deployed bb1aab6 with MkDocs version: 1.6.1
2026-01-31 Add dev plan
2026-01-31 Readme: Add plan to readme
2026-01-31 dev-log: Add 1-29 dev log
2026-01-31 .gitignore: Add LLM files
2026-01-31 Add pyproject file
2026-01-31 Add basic file structure
2026-01-31 Add config
2026-01-31 Add hrr download
2026-01-31 Rearrange software folders
2026-01-31 Update dev plan
2026-01-31 Add unit tests
2026-01-31 Add basic CI
2026-01-31 Add Initial Download Scripts for HRRR (#28)
    * Add pyproject file
    * Add basic file structure
    * Add config
    * Add hrr download
    * Rearrange software folders
    * Update dev plan
2026-01-31 Add era5
2026-01-31 Update dev plan for era5
2026-01-31 Add test
2026-01-31 Add era5 readme setup
2026-01-31 test
2026-01-31 Fix ruff warnings
2026-01-31 Ignore era5 data filers
2026-01-31 Add ERA5 Data Download (#29)
    * Add era5
    * Update dev plan for era5
    * Update
    * Add test
    * Add era5 readme setup
    * test
2026-01-31 Add IEM data
2026-01-31 Add data loaders
2026-01-31 Add dataloaders
2026-01-31 .gitignore: Add parquest files
2026-01-31 Fix ruff
2026-01-31 Add data loaders (#30)
2026-01-31 add ruff
2026-01-31 Add Initial GNNs (#31)
2026-01-31 Update plan
2026-01-31 Deployed 8728a11 with MkDocs version: 1.6.1
2026-01-31 Add training scripts
2026-01-31 Deploy preview for PR 32 🛫
2026-02-02 Traing updates
2026-02-02 Readme: Add ultrasonic transducer picture
    Updated the description of the ultrasonic anemometer project and added a new image.
2026-06-22 Readme: Remove hardware focus
2026-06-30 Add intro + intial modeling attempt
